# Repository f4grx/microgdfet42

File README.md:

# microgdfet42
Micro version of Travis Goodspeed's GoodFET42

http://goodfet.sourceforge.net/hardware/goodfet42/

Board made with kicad 5.1

Project is standalone, all the required schematic and footprint parts are in the
local libraries, so there is no dependency on any external kicad library.

Can be ordered at oshpark: https://oshpark.com/shared_projects/S5LdunO2

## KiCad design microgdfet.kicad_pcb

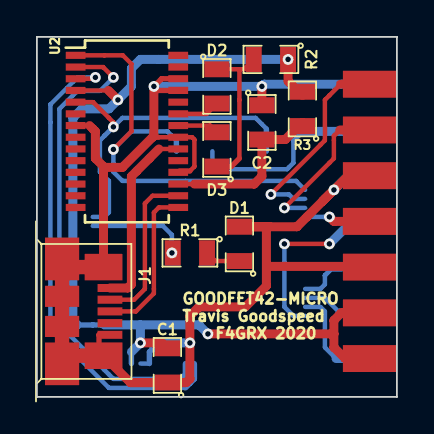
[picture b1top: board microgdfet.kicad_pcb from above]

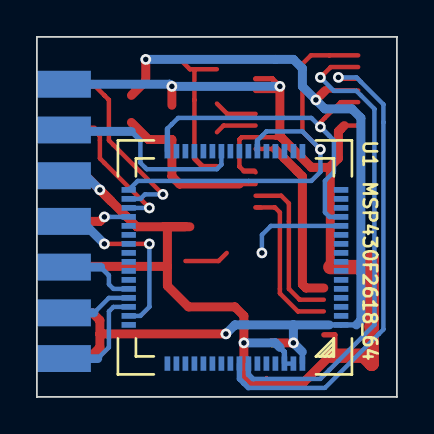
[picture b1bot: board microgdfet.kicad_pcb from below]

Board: 2 copper layers, 20.0 x 20.0 mm, 12 parts (2 on the bottom side), 23 nets.

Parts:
C1, C2: 100n; 0805
D1, D2, D3: LED; 0805
J1: USB_MICROB; USB_MICROB_MOLEX
P1: CONN_2x7; PIN_ARRAY_7X2_SIDE
R1, R2: 330; 0805
R3: 0R; 0805
U1: MSP430F2618_64; TQFP64
U2: FT232R_SSOP; TSSOP28

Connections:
/3V3OUT: C2.2, R3.1, U2.17
/BSL_PCINMCUOUT: U1.13, U1.32, U2.5
/BSL_PCOUTMCUIN: U1.22, U1.33, U2.1
/BSL_RST: U1.58, U2.2
/BSL_TCK: U1.57, U2.3
/LED: R1.2, U1.12
/RXIN: P1.12, U1.35
/RXLED: D3.2, U2.22
/TCK: P1.7, U1.47
/TDI: P1.3, U1.45
/TDO: P1.1, U1.46
/TMS: P1.5, U1.44
/TST: P1.8, U1.36
/TXLED: D2.2, U2.23
/TXOUT: P1.14, U1.34
/USBDM: J1.2, U2.16
/USBDP: J1.3, U2.15
/VBUS: J1.1, U2.20
/VCC: C1.2, P1.2, P1.4, R2.1, R3.2, U1.1, U1.64, U2.4
/~RST~: P1.11, U1.26
GND: C1.1, C2.1, D1.2, J1.5, J1.6, P1.6, P1.9, P1.10, P1.13, U1.62, U1.63, U2.7, U2.18, U2.21, U2.25, U2.26
unnamed: D1.1, R1.1
unnamed: D2.1, D3.1, R2.2

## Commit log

2020-02-10 Initial release
2020-02-10 Update README.md
    fix kicad version
